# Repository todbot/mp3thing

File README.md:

mp3thing
========

mp3 player controller for cheap commercial screenless mp3 players

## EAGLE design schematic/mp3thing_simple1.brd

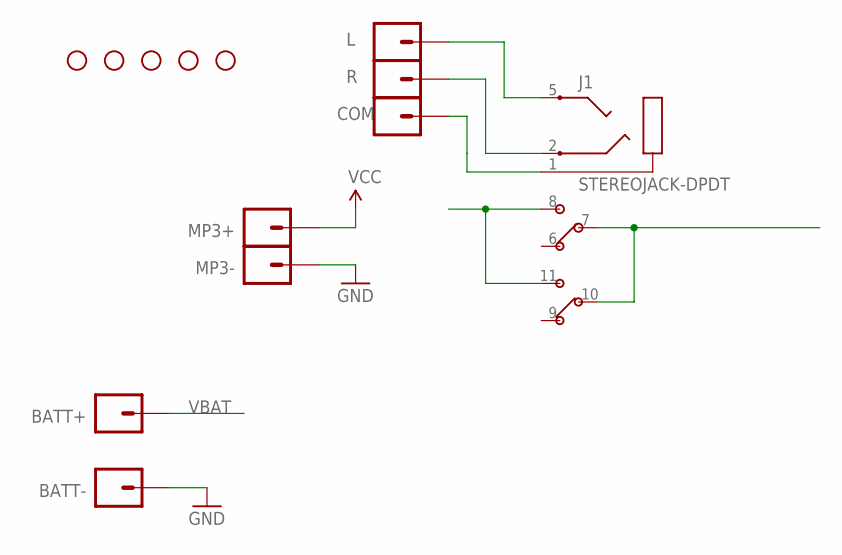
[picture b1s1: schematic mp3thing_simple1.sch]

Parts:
BATT+: M01PTH; 1X01
BATT-: M01PTH; 1X01
COM: M01PTH; 1X01
J1: STEREOJACK-DPDT; STX3100-9C
JP1, JP2, JP3, JP4, JP5: STAND-OFF
L: M01PTH; 1X01
MP3+, MP3-: M01PTH; 1X01
R: M01PTH; 1X01

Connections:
GND: BATT-.1, MP3-.1
unnamed: COM.1, J1.1
unnamed: J1.5, L.1
unnamed: J1.2, R.1
VBAT: BATT+.1, J1.7, J1.10
VCC: J1.8, J1.11, MP3+.1

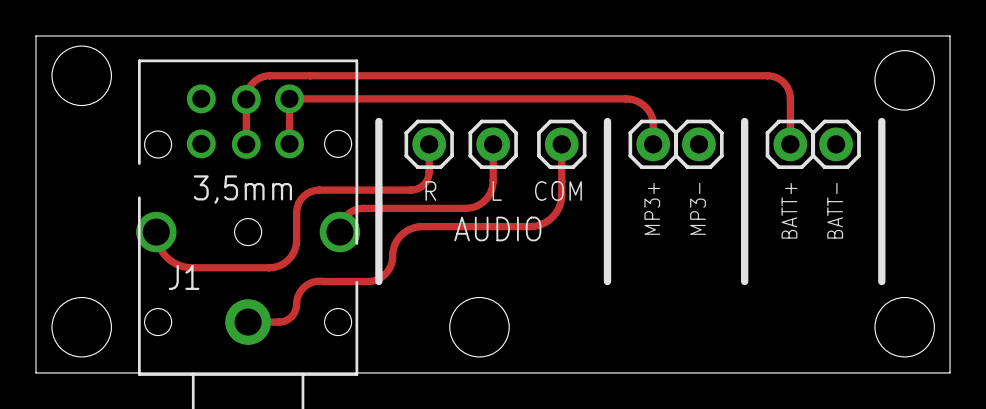
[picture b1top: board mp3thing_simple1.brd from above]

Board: 2 copper layers, 50.8 x 18.7 mm, 13 parts (0 on the bottom side), 6 nets.

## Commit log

2012-06-24 added files to repo
2012-06-26 added wiring diags
2012-06-26 removed autosave files
2013-01-26 added more docs
2013-02-03 changed to attiny25
2013-04-13 added new polaroid clip twiddler function
2014-07-15 stuff for gallery opening
2014-07-16 mp3player1_button is version in gallery boxes
